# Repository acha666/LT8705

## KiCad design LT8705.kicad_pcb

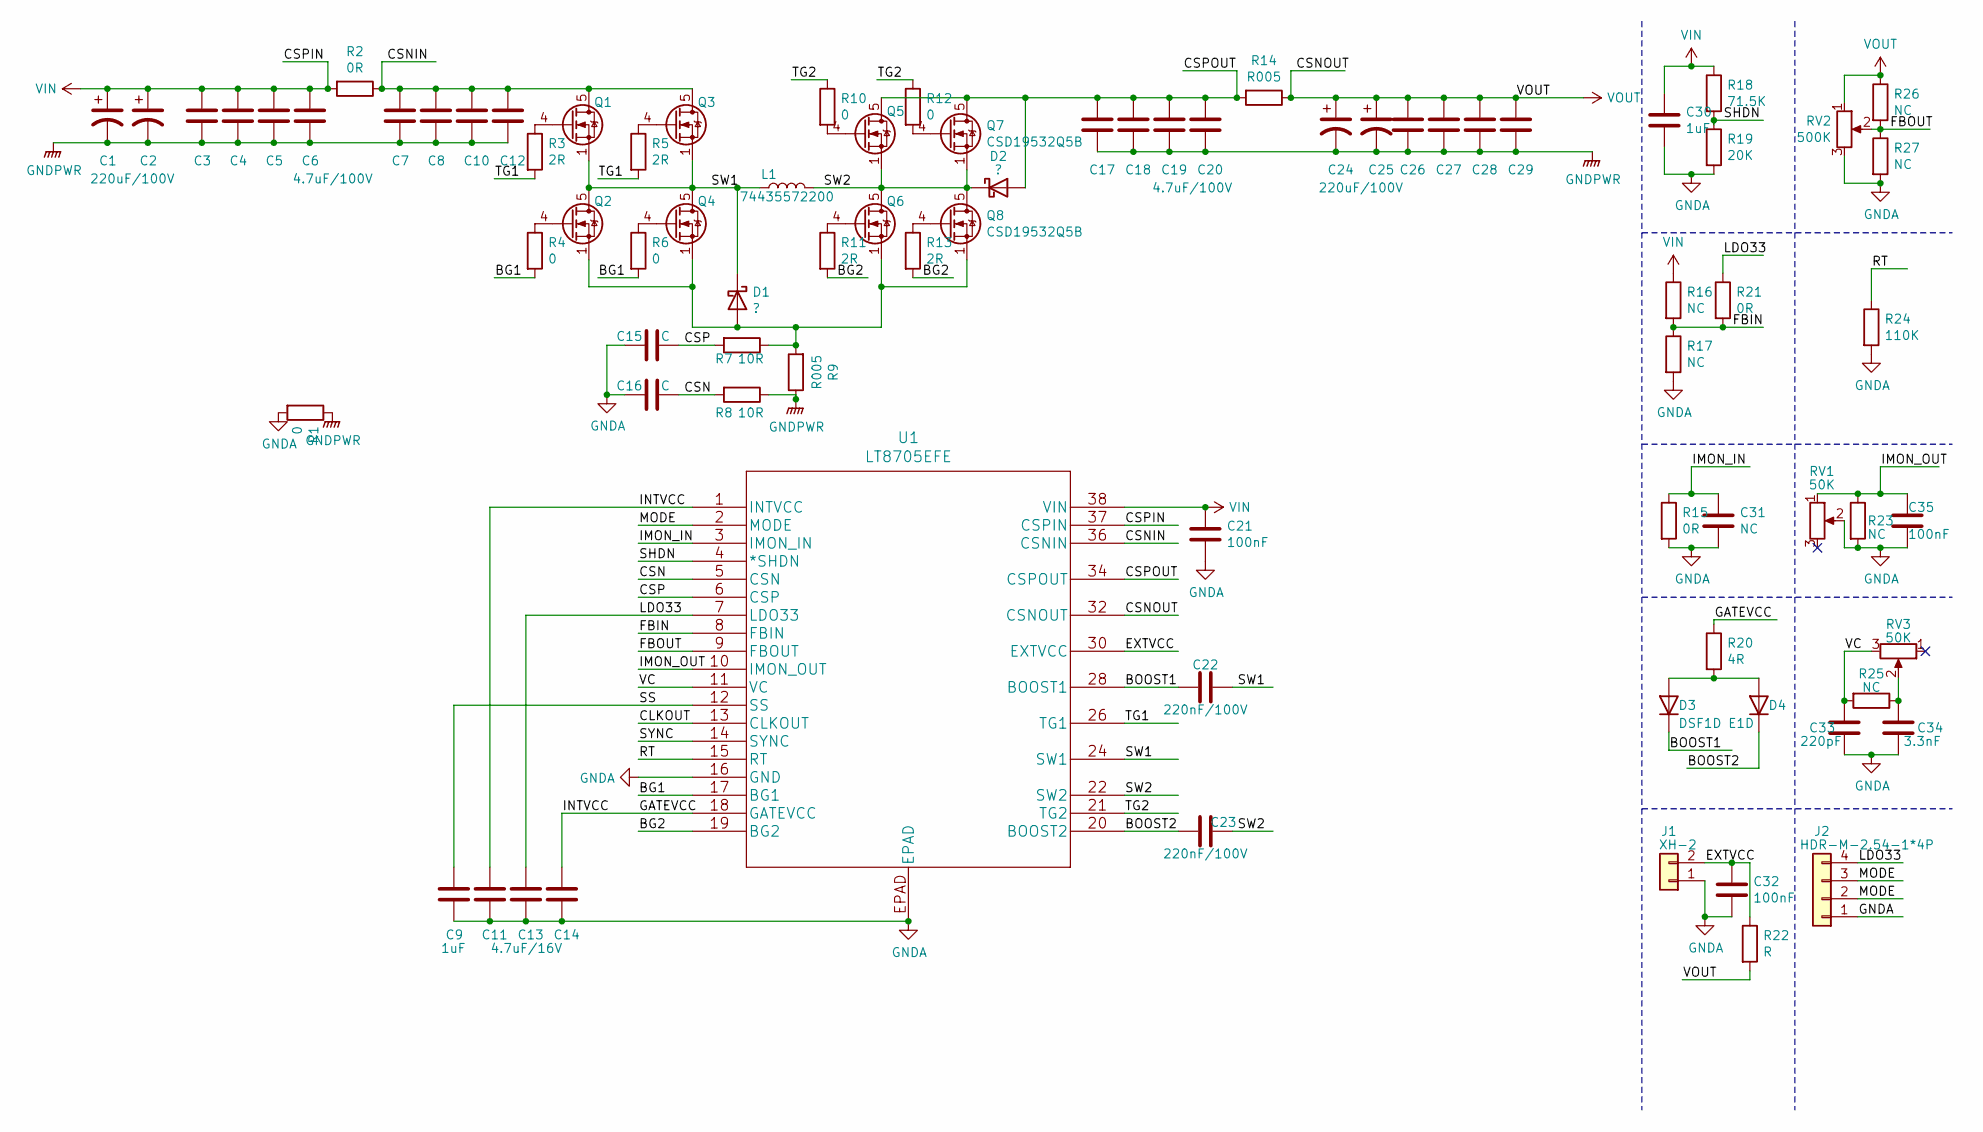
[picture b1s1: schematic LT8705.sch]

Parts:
C1, C2, C24, C25: 220uF/100V; C_Radial_D12.5mm_H25.0mm_P5.00mm
C3, C4, C5, C6, C7, C8, C10, C12: 4.7uF/100V; C_1210_3225Metric_Pad1.33x2.70mm_HandSolder
C9, C30: 1uF; C_0603_1608Metric_Pad1.05x0.95mm_HandSolder
C11, C13, C14: 4.7uF/16V; C_0603_1608Metric_Pad1.05x0.95mm_HandSolder
C15, C16: C; C_0603_1608Metric_Pad1.05x0.95mm_HandSolder
C17, C18, C19, C20, C26, C27, C28, C29: 4.7uF/100V; C_1210_3225Metric_Pad1.42x2.65mm_HandSolder
C21, C32, C35: 100nF; C_0603_1608Metric_Pad1.05x0.95mm_HandSolder
C22, C23: 220nF/100V; C_0805_2012Metric_Pad1.15x1.40mm_HandSolder
C31: NC; C_0603_1608Metric_Pad1.05x0.95mm_HandSolder
C33: 220pF; C_0603_1608Metric_Pad1.05x0.95mm_HandSolder
C34: 3.3nF; C_0603_1608Metric_Pad1.05x0.95mm_HandSolder
D1, D2: ?; D_SMA-SMB_Universal_Handsoldering
D3, D4: DSF1D E1D; D_SOD-123
J1: XH-2; JST_XH_B2B-XH-A_1x02_P2.50mm_Vertical
J2: HDR-M-2.54-1*4P; PinHeader_1x04_P2.54mm_Vertical
L1: 74435572200; IND_74435572200
Q1, Q2, Q7, Q8: CSD19532Q5B; TDSON-8-1
Q3, Q4, Q5, Q6: NC; TDSON-8-1
R1, R4, R6, R10, R12: 0; R_0603_1608Metric_Pad0.98x0.95mm_HandSolder
R2: 0R; R_0612_1632Metric
R3, R5, R11, R13: 2R; R_0603_1608Metric_Pad0.98x0.95mm_HandSolder
R7, R8: 10R; R_0603_1608Metric_Pad0.98x0.95mm_HandSolder
R9: R005; R_1225_3263Metric
R14: R005; R_0612_1632Metric
R15, R21: 0R; R_0603_1608Metric_Pad0.98x0.95mm_HandSolder
R16, R17, R23, R25, R26, R27: NC; R_0603_1608Metric_Pad0.98x0.95mm_HandSolder
R18: 71.5K; R_0603_1608Metric_Pad0.98x0.95mm_HandSolder
R19: 20K; R_0603_1608Metric_Pad0.98x0.95mm_HandSolder
R20: 4R; R_0603_1608Metric_Pad0.98x0.95mm_HandSolder
R22: R; R_0603_1608Metric_Pad0.98x0.95mm_HandSolder
R24: 110K; R_0603_1608Metric_Pad0.98x0.95mm_HandSolder
RV1, RV3: 50K; Potentiometer_Bourns_3296W_Vertical
RV2: 500K; Potentiometer_Bourns_3296W_Vertical
U1: LT8705EFE

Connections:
/BG1: R4.2, R6.2, U1.17 (BG1)
/BG2: R11.2, R13.2, U1.19 (BG2)
/BOOST1: C22.2, D3.1 (K), U1.28 (BOOST1)
/BOOST2: C23.2, D4.1 (K), U1.20 (BOOST2)
/CLKOUT: U1.13 (CLKOUT)
/CSN: C16.1, R8.2, U1.5 (CSN)
/CSNIN: C7.1, C8.1, C10.1, C12.1, Q1.5 (D), Q3.5 (D), R2.1, U1.36 (CSNIN)
/CSP: C15.1, R7.2, U1.6 (CSP)
/CSPOUT: C17.1, C18.1, C19.1, C20.1, D2.2 (A), Q5.5 (D), Q7.5 (D), R14.2, U1.34 (CSPOUT)
/EXTVCC: C32.1, J1.2, R22.1, U1.30 (EXTVCC)
/FBIN: R16.2, R17.1, R21.2, U1.8 (FBIN)
/FBOUT: R26.2, R27.1, RV2.2, U1.9 (FBOUT)
/GATEVCC: C11.1, C14.1, R20.1, U1.1 (INTVCC), U1.18 (GATEVCC)
/IMON_IN: C31.1, R15.1, U1.3 (IMON_IN)
/IMON_OUT: C35.1, R23.1, RV1.1, U1.10 (IMON_OUT)
/LDO33: C13.1, J2.4, R21.1, U1.7 (LDO33)
/MODE: J2.2, J2.3, U1.2 (MODE)
/RT: R24.1, U1.15 (RT)
/SHDN: R18.2, R19.1, U1.4 (*SHDN)
/SS: C9.1, U1.12 (SS)
/SW1: C22.1, D1.1 (K), L1.1, Q1.1 (S), Q1.2 (S), Q1.3 (S), Q2.5 (D), Q3.1 (S), Q3.2 (S), Q3.3 (S), Q4.5 (D), U1.24 (SW1)
/SW2: C23.1, D2.1 (K), L1.2, Q5.1 (S), Q5.2 (S), Q5.3 (S), Q6.5 (D), Q7.1 (S), Q7.2 (S), Q7.3 (S), Q8.5 (D), U1.22 (SW2)
/SYNC: U1.14 (SYNC)
/TG1: R3.2, R5.2, U1.26 (TG1)
/TG2: R10.1, R12.1, U1.21 (TG2)
/VC: C33.1, R25.2, RV3.3, U1.11 (VC)
GNDA: C9.2, C11.2, C13.2, C14.2, C15.2, C16.2, C21.2, C30.2, C31.2, C32.2, C33.2, C34.2, C35.2, J1.1, J2.1, R1.2, R15.2, R17.2, R19.2, R23.2, R24.2, R27.2, RV1.2, RV2.3, U1.16 (GND), U1.EPAD
GNDPWR: C1.2, C2.2, C3.2, C4.2, C5.2, C6.2, C7.2, C8.2, C10.2, C12.2, C17.2, C18.2, C19.2, C20.2, C24.2, C25.2, C26.2, C27.2, C28.2, C29.2, R1.1, R8.1, R9.1
unnamed: C34.1, R25.1, RV3.2
unnamed: D1.2 (A), Q2.1 (S), Q2.2 (S), Q2.3 (S), Q4.1 (S), Q4.2 (S), Q4.3 (S), Q6.1 (S), Q6.2 (S), Q6.3 (S), Q8.1 (S), Q8.2 (S), Q8.3 (S), R7.1, R9.2
unnamed: D3.2 (A), D4.2 (A), R20.2
unnamed: Q1.4 (G), R3.1
unnamed: Q2.4 (G), R4.1
unnamed: Q3.4 (G), R5.1
unnamed: Q4.4 (G), R6.1
unnamed: Q5.4 (G), R10.2
unnamed: Q6.4 (G), R11.1
unnamed: Q7.4 (G), R12.2
unnamed: Q8.4 (G), R13.1
VD: C24.1, C25.1, C26.1, C27.1, C28.1, C29.1, R14.1, R22.2, R26.1, RV2.1, U1.32 (CSNOUT)
VDD: C1.1, C2.1, C3.1, C4.1, C5.1, C6.1, C21.1, C30.1, R2.2, R16.1, R18.1, U1.37 (CSPIN), U1.38 (VIN)

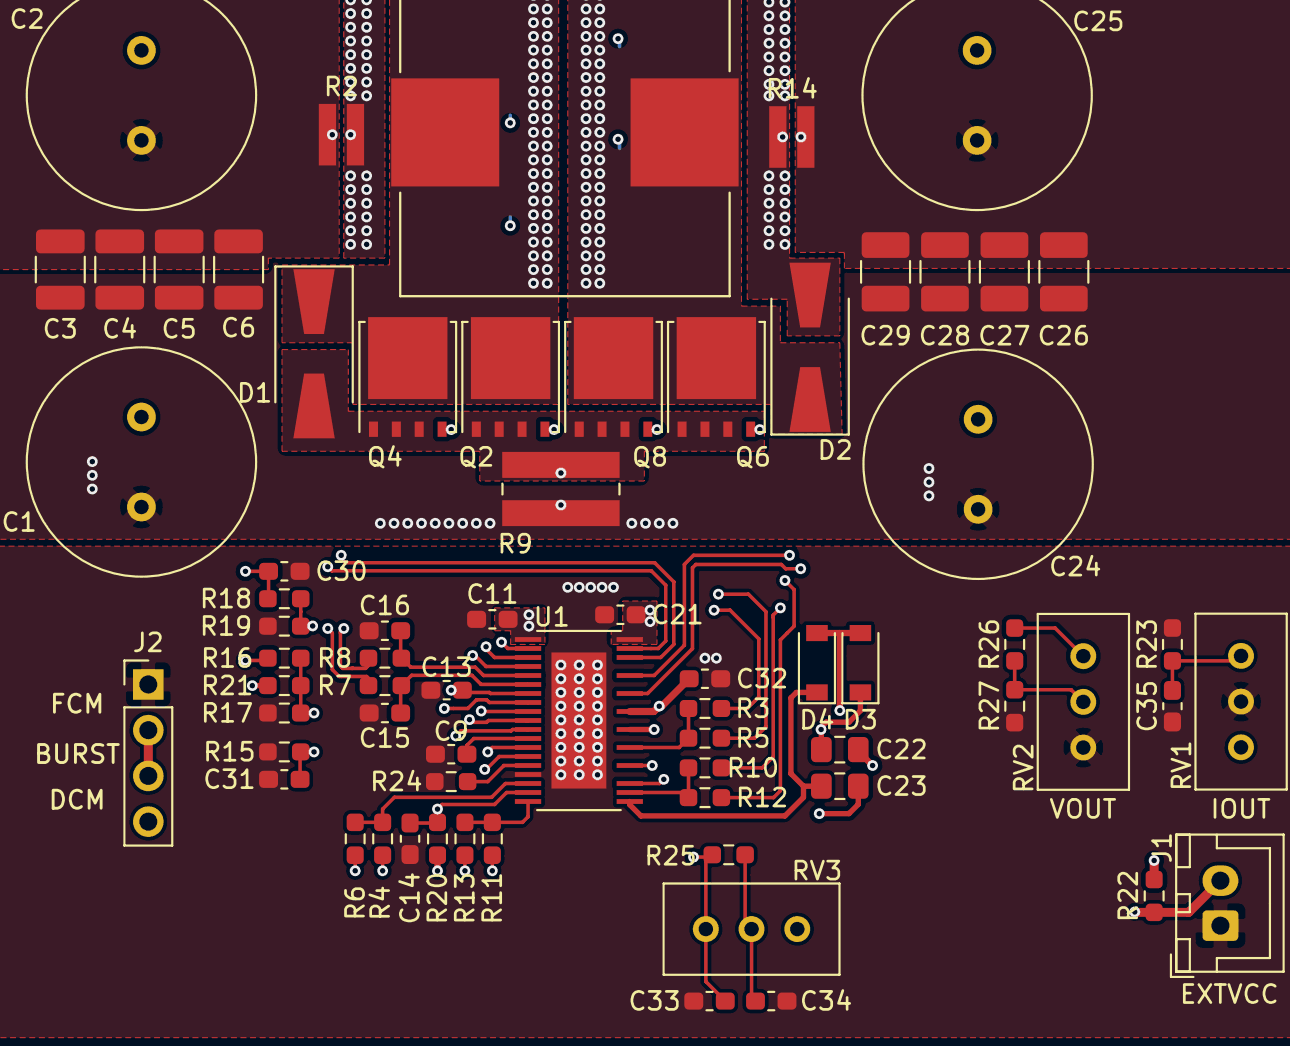
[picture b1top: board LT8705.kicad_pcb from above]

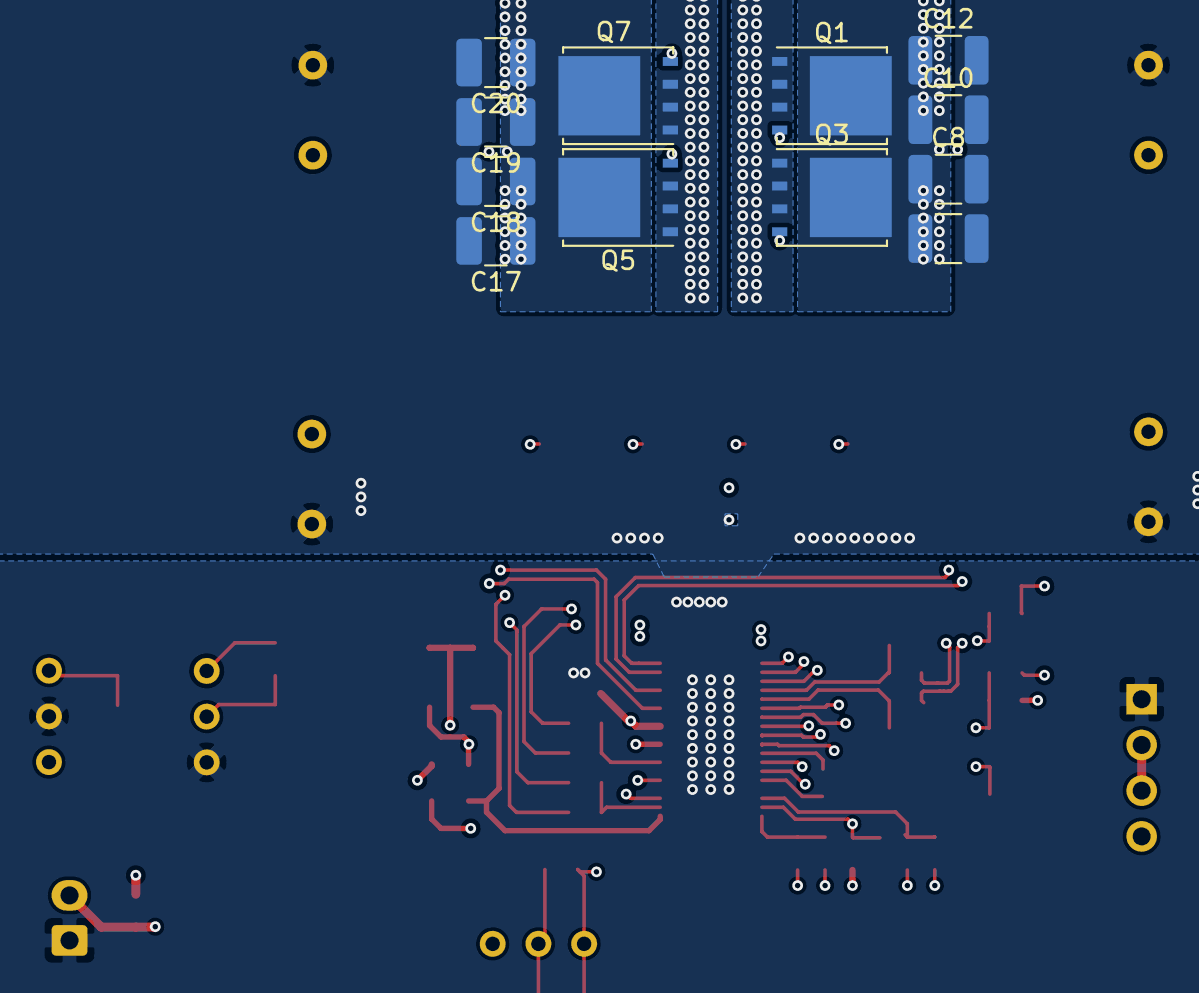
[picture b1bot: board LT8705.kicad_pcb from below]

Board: 4 copper layers, 80 parts (12 on the bottom side), 39 nets.

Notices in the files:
parts and their libraries:
Copyright 2021 Accelerated Designs. All rights reserved.
